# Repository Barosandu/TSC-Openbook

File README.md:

# Proiect Ariton Alexandru -- TSC -- Openbook

### Pasii de implementare
* Am creat schematicul 2D.
* Am creat PCB-ul, am intampinat niste erori:
    * **Via(hole) error** la componenta USB: am modificat footprint-ul componentei.
    * **Wire to wire error**: am rutat firele manual
* Am atribuit fiecarei componente din library cate un model 3D, si am creat placa 3d (*Push to 3D*)
* Am creat modelele pentru Display si Baterie dupa specificatiile din datasheeturi

### Diagrama block
* salvata in folder cu numele BlockSchematic.png
* Pini ESP32-C6
    * Interfetele SPI -- folosite pentru conectarea la Display
    * Este conectat la senzorul BME688 prin I2C.
    * E conectat la portul USB-C prin interfata USB
    * E conectat la butoane prin porturile GPIO

## Configurație pini ESP32-C6

| Componentă      | Pin ESP32-C6        |
|----------------|---------------------|
| Display SPI    | MOSI, CLK, CS, DC   |
| BME688         | SDA, SCL (I2C)      |
| Butoane        | GPIO1, GPIO2, GPIO3 |
| USB-C          | D+, D−, VBUS        |

### Componente Folosite

MCU: ESP32-C6-WROOM-1 (sau echivalent), datorita integrarii Wi-Fi 6, BLE 5 si a puterii de procesare ridicate.

Afisaj: Waveshare WSH-13187, e-Paper de 7.5 inch (sau echivalent), cu rezolutie 800x480.

Senzori: Bosch BME688 – pentru temperatura, umiditate, presiune si calitatea aerului.

Baterie: Baterie Li-Polimer de 2500mAh, cu circuit de protectie integrat.

Indicator nivel baterie (Fuel Gauge): Maxim MAX17048 sau echivalent.

Circuit de incarcare: Microchip MCP73831 sau echivalent.

Butoane: Comutatoare tactile Panasonic EVQ-Q2A03W (sau echivalent).

Conector USB-C: Amphenol 12401641E4R (sau echivalent).

Conector pentru card microSD: Attend Tech 112A-TAAR-R03 (sau echivalent).

Ceas in timp real (RTC): DS3231 (sau echivalent), cu supercapacitor pentru backup.

Conector Qwiic/Stemma: pentru conectarea rapida a senzorilor compatibili.

| Componenta                                      | Link                                                                 |
|------------------------------------------------|----------------------------------------------------------------------|
| adafruit_led                                   | [Link](https://www.snapeda.com/parts/KP-1608SURCK/Kingbright/view-part/?company=Politehnica+University+of+Buch&welcome=home&ref=search&t=LED+0603) |
| Button_customv1                                | [Link](https://industry.panasonic.com/global/en/products/control/switch/light-touch/number/evqpuj02k) |
| Eagle_ltspice_c                                | [Link](https://componentsearchengine.com/part-view/0402WGF3001TCE/UNI-ROYAL(Uniroyal%20Elec)) |
| ESP32_WROVER_AVX—SD0805S020S1R0                | [Link](https://ro.mouser.com/ProductDetail/KYOCERA-AVX/SD0805S020S1R0?qs=jCA%252BPfw4LHbpkAoSnwrdjw%3D%3D) |
| ESP32_WROVER_BME680_BME680                     | [Link](https://www.snapeda.com/parts/BME680/Bosch/view-part/?welcome=home) |
| ESP32_WROVER_EAGLE-LTSPICE_R                   | [Link](https://componentsearchengine.com/part-view/R0402%201%25%20100%20K%20(RC0402FR-07100KL)/YAGEO) |
| RCL_CPOL-EU                                    | [Link](https://www.snapeda.com/parts/TAJB475K025RNJ/AVX/view-part/?t=capacitor%203528&con_ref=None) |
| SJ                                             | [Link](https://grabcad.com/library/solder-jumpers-1) |
| R-URI                                          | [Link](https://componentsearchengine.com/part-view/R0402%201%25%20100%20K%20(RC0402FR-07100KL)/YAGEO) |
| ESP32_WROVER_SPARKFUN-DISCRETESEMI_MOSFET_PCH | [Link](https://componentsearchengine.com/part-view/DMG2305UX-7/Diodes%20Incorporated) |
| ESP32_WROVER_SPARKFUN-IC-POWER_MCP73831       | [Link](https://eu.mouser.com/ProductDetail/Microchip-Technology/MCP73831T-2ACI-OT?qs=yUQqVecv4qvbBQBGbHx0Mw%3D%3D) |
| TP                                             | Facut Manual |
| FH34SRJ-24S-0.5SH_99_                          | [Link](https://componentsearchengine.com/part-view/FH34SRJ-24S-0.5SH(99)/Hirose) |
| MAX17048G+T10                                  | [Link](https://www.snapeda.com/parts/MAX17048G+T10/Analog+Devices/view-part/) |
| SAMACSYS_PARTS_USB4110-GF-A                    | [Link](https://componentsearchengine.com/part-view/USB4110-GF-A/GCT%20(GLOBAL%20CONNECTOR%20TECHNOLOGY)) |
| QWIIC_CONNECTOR                                | [Link](https://www.snapeda.com/parts/PRT-14417/SparkFun%20Electronics/view-part/?t=QWIIC_CONNECTORJS-1MM) |
| 112A-TAAR-R03_ATTEND                           | [Link](https://componentsearchengine.com/part-view/112A-TAAR-R03%20ATTEND/ATTEND) |
| 744043680IND_4828-WE-TPC_WRE                   | [Link](https://componentsearchengine.com/part-view/744043680/W%C3%BCrth%20Elektronik) |
| BD5229G-TR                                     | [Link](https://componentsearchengine.com/part-view/BD5229G-TR/ROHM%20Semiconductor) |
| CPH3225A                                       | [Link](https://componentsearchengine.com/part-view/CPH3225A/Seiko%20Semiconductors) |
| DS3231SN#                                      | [Link](https://componentsearchengine.com/part-view/DS3231SN%23/Analog%20Devices) |
| ESP32-C6-WROOM-1-N8                            | [Link](https://componentsearchengine.com/part-view/ESP32-C6-WROOM-1-N8/Espressif%20Systems) |
| MBR0530                                        | [Link](https://componentsearchengine.com/part-view/MBR0530/onsemi) |
| SI1308EDL-T1-GE3                               | [Link](https://componentsearchengine.com/part-view/SI1308EDL-T1-GE3/Vishay) |
| USBLC6-2SC6Y                                   | [Link](https://componentsearchengine.com/part-view/USBLC6-2SC6Y/STMicroelectronics) |
| W25Q512JVEIQ                                   | [Link](https://componentsearchengine.com/part-view/W25Q512JVEIQ/Winbond) |
| XC6220A331MR-G                                 | [Link](https://componentsearchengine.com/part-view/XC6220A331MR-G/Torex) |

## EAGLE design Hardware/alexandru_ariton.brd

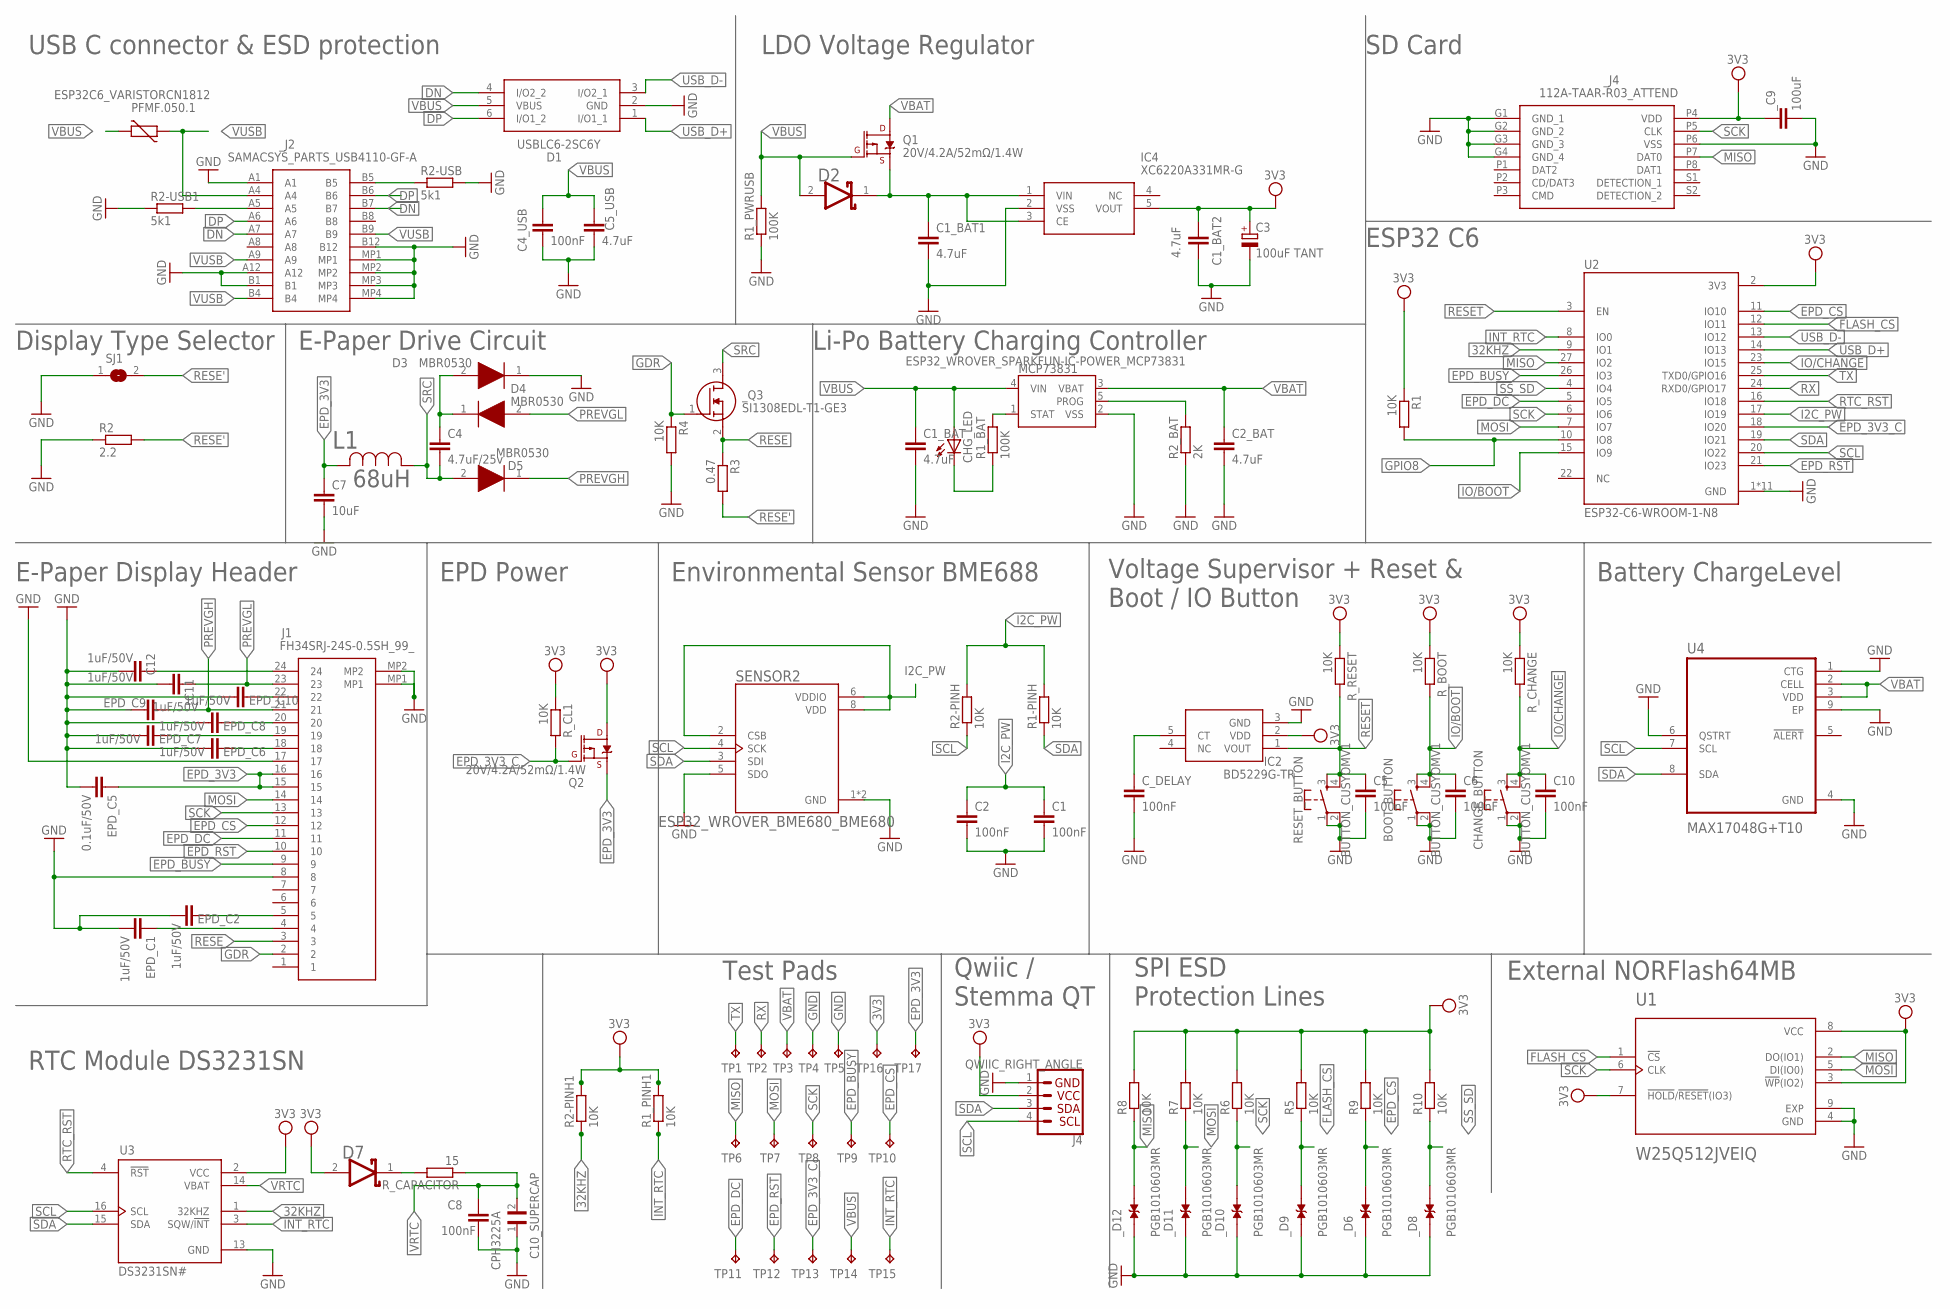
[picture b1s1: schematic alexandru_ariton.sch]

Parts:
BOOT_BUTTON: BUTTON_CUSYOMV1; MYBUTTON
C1, C2, C4_USB, C8: 100nF; EAGLE-LTSPICE_C0402
C1_BAT, C1_BAT1, C1_BAT2, C2_BAT, C5_USB: 4.7uF; EAGLE-LTSPICE_C0402
C3: 100uF TANT; RCL_CT3528
C4: 4.7uF/25v; EAGLE-LTSPICE_C0402
C5, C6, C10: 100nF; ESP32_WROVER_EAGLE-LTSPICE_C0402
C7: 10uF; EAGLE-LTSPICE_C0402
C10_SUPERCAP: CPH3225A; CAPCP3225X100N
C11, C12: 1uF/50V; EAGLE-LTSPICE_C0402
CHANGE_BUTTON: BUTTON_CUSYOMV1; MYBUTTON
CHG_LED: ADAFRUIT_LEDCHIP-LED0603; ADAFRUIT_CHIP-LED0603
C_DELAY: 100nF; ESP32_WROVER_EAGLE-LTSPICE_C0402
D1: USBLC6-2SC6Y; SOT95P280X145-6N
D2, D7: ESP32_WROVER_AVX---SD0805S020S1R0_AVX_SD0805S020S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; ESP32_WROVER_AVX---SD0805S020S1R0_AVX_SD0805S020S1R0_0
D3, D4, D5: MBR0530; SOD3716X135N
EPD_C1, EPD_C2, EPD_C6, EPD_C7, EPD_C8, EPD_C9, EPD_C10: 1uF/50V; EAGLE-LTSPICE_C0402
EPD_C5: 0.1uF/50V; EAGLE-LTSPICE_C0402
IC2: BD5229G-TR; SOT95P280X125-5N
IC4: XC6220A331MR-G; SOT95P280X120-5N
J1: FH34SRJ-24S-0.5SH_99_; FH34SRJ24S05SH99
J4: QWIIC_RIGHT_ANGLE; JST04_1MM_RA
L1: 68uH; IND_4828-WE-TPC_WRE
MCP73831: ESP32_WROVER_SPARKFUN-IC-POWER_MCP73831; ESP32_WROVER_SPARKFUN-IC-POWER_SOT23-5
PFMF.050.1: ESP32C6_VARISTORCN1812; ESP32C6_VARISTOR_CT/CN1812
Q1, Q2: 20V/4.2A/52mΩ/1.4W; ESP32_WROVER_SPARKFUN-DISCRETESEMI_SOT23-3
R1, R1-PINH, R1_PINH1, R2-PINH, R2-PINH1, R4, R5, R6, R7, R8, R9, R10: 10K; ESP32_WROVER_EAGLE-LTSPICE_R0402
R1_BAT, R1_PWRUSB: 100K; ESP32_WROVER_EAGLE-LTSPICE_R0402
R2: 2.2; ESP32_WROVER_EAGLE-LTSPICE_R0402
R2-USB, R2-USB1: 5k1; ESP32_WROVER_EAGLE-LTSPICE_R0402
R2_BAT: 2K; ESP32_WROVER_EAGLE-LTSPICE_R0402
R3: 0.47; ESP32_WROVER_EAGLE-LTSPICE_R0402
RESET_BUTTON: BUTTON_CUSYOMV1; MYBUTTON
R_BOOT: 10K; ESP32_WROVER_EAGLE-LTSPICE_R0402
R_CAPACITOR: 15; ESP32_WROVER_EAGLE-LTSPICE_R0402
R_CHANGE: 10K; ESP32_WROVER_EAGLE-LTSPICE_R0402
R_CL1: 10K; ESP32_WROVER_EAGLE-LTSPICE_R0402
R_RESET: 10K; ESP32_WROVER_EAGLE-LTSPICE_R0402
SENSOR2: ESP32_WROVER_BME680_BME680; ESP32_WROVER_BME680_PSON80P300X300X100-8N
SJ1: SJ
TP1, TP2, TP3, TP4, TP5, TP6, TP7, TP8, TP9, TP10, TP11, TP12, TP13, TP14, TP15, TP16, TP17: TPTP20R; TP20R
U1: W25Q512JVEIQ; SON127P600X800X80-9N
U2: ESP32-C6-WROOM-1-N8; XCVR_ESP32-C6-WROOM-1-N8
U3: DS3231SN#; SOIC127P1032X265-16N
U4: MAX17048G+T10; SON50P200X200X80-9N
_C9: 100uF; EAGLE-LTSPICE_C0402
_D6, _D8, _D9, _D10, _D11, _D12: PGB1010603MR; DIOC1608X36N
_J2: SAMACSYS_PARTS_USB4110-GF-A; SAMACSYS_PARTS_USB4110GFA
_J4: 112A-TAAR-R03_ATTEND; 112ATAARR03ATTEND
_Q3: SI1308EDL-T1-GE3; SOT65P210X110-3N

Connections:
3V3: C1_BAT2.1, C3.+, D7.2 (ANODE), IC2.2 (VDD), IC4.5 (VOUT), J4.2, Q2.3 (D), R1.1, R1_PINH1.2, R2-PINH1.2, R5.2, R6.2, R7.2, R8.2, R9.2, R10.2, R_BOOT.1, R_CHANGE.1, R_CL1.1, R_RESET.1, TP16.TP, U1.3 (!WP!(IO2)), U1.7 (!HOLD!/!RESET!(IO3)), U1.8 (VCC), U2.2 (3V3), U3.2 (VCC), _C9.1, _J4.P4 (VDD)
32KHZ: R2-PINH1.1, U2.9 (IO1), U3.1 (32KHZ)
DN: D1.4 (I/O2_2), _J2.A7, _J2.B7
DP: D1.6 (I/O1_2), _J2.A6, _J2.B6
EPD_3V3: C7.1, EPD_C5.1, J1.15, J1.16, L1.2, Q2.2 (S), TP17.TP
EPD_3V3_C: Q2.1 (G), R_CL1.2, TP13.TP, U2.18 (IO20)
EPD_BUSY: J1.9, TP9.TP, U2.26 (IO3)
EPD_CS: J1.12, R9.1, TP10.TP, U2.11 (IO10), _D6.2
EPD_DC: J1.11, TP11.TP, U2.5 (IO5)
EPD_RST: J1.10, TP12.TP, U2.21 (IO23)
FLASH_CS: R5.1, U1.1 (!CS), U2.12 (IO11), _D9.2
GDR: J1.2, R4.1, _Q3.1 (G)
GND: BOOT_BUTTON.1, BOOT_BUTTON.2, C1.2, C1_BAT.2, C1_BAT1.2, C1_BAT2.2, C2.2, C2_BAT.2, C3.-, C4_USB.2, C5.2, C5_USB.2, C6.2, C7.2, C8.2, C10.2, C10_SUPERCAP.1, C11.2, C12.2, CHANGE_BUTTON.1, CHANGE_BUTTON.2, C_DELAY.2, D1.2 (GND), D3.1 (K), EPD_C1.2, EPD_C2.2, EPD_C5.2, EPD_C6.2, EPD_C7.2, EPD_C8.2, EPD_C9.2, EPD_C10.2, IC2.3 (GND), IC4.2 (VSS), J1.8, J1.17, J1.MP1, J1.MP2, J4.1, MCP73831.2 (VSS), R1_PWRUSB.1, R2.1, R2-USB.2, R2-USB1.1, R2_BAT.1, R4.2, RESET_BUTTON.1, RESET_BUTTON.2, SENSOR2.1 (GND), SENSOR2.5 (SDO), SENSOR2.7 (GND), SJ1.1, TP4.TP, TP5.TP, U1.4 (GND), U1.9 (EXP), U2.1 (GND), U2.28 (GND), U2.29_1 (GND), U2.29_2 (GND), U2.29_3 (GND), U2.29_4 (GND), U2.29_5 (GND), U2.29_6 (GND), U2.29_7 (GND), U2.29_8 (GND), U2.29_9 (GND), U3.13 (GND), U4.1 (CTG), U4.4 (GND), U4.6 (QSTRT), U4.9 (EP), _C9.2, _D6.1, _D8.1, _D9.1, _D10.1, _D11.1, _D12.1, _J2.A1, _J2.A12, _J2.B1, _J2.B12, _J2.MP1, _J2.MP2, _J2.MP3, _J2.MP4, _J4.G1 (GND_1), _J4.G2 (GND_2), _J4.G3 (GND_3), _J4.G4 (GND_4), _J4.P6 (VSS)
GPIO8: R1.2, U2.10 (IO8)
I2C_PW: C1.1, C2.1, R1-PINH.2, R2-PINH.2, SENSOR2.2 (CSB), SENSOR2.6 (VDDIO), SENSOR2.8 (VDD), U2.17 (IO19)
INT_RTC: R1_PINH1.1, TP15.TP, U2.8 (IO0), U3.3 (SQW/!INT)
IO/BOOT: BOOT_BUTTON.3, BOOT_BUTTON.4, C6.1, R_BOOT.2, U2.15 (IO9)
IO/CHANGE: C10.1, CHANGE_BUTTON.3, CHANGE_BUTTON.4, R_CHANGE.2, U2.23 (IO15)
MISO: R8.1, TP6.TP, U1.2 (DO(IO1)), U2.27 (IO2), _D12.2, _J4.P7 (DAT0)
MOSI: J1.14, R7.1, TP7.TP, U1.5 (DI(IO0)), U2.7 (IO7), _D11.2
unnamed: R2-USB.1, _J2.B5
unnamed: R2-USB1.2, _J2.A5
unnamed: C1_BAT1.1, D2.1 (CATHODE), IC4.1 (VIN), IC4.3 (CE), Q1.2 (S)
unnamed: MCP73831.1 (STAT), R1_BAT.2
unnamed: C4.1, D3.2 (A), D4.1 (K)
unnamed: CHG_LED.C, R1_BAT.1
unnamed: MCP73831.5 (PROG), R2_BAT.2
unnamed: C12.1, J1.24
unnamed: EPD_C10.1, J1.22
unnamed: EPD_C8.1, J1.20
unnamed: EPD_C7.1, J1.19
unnamed: EPD_C6.1, J1.18
unnamed: D7.1 (CATHODE), R_CAPACITOR.2
unnamed: C_DELAY.1, IC2.5 (CT)
unnamed: EPD_C1.1, J1.4
unnamed: EPD_C2.1, J1.5
PREVGH: D5.1 (K), EPD_C9.1, J1.21
PREVGL: C11.1, D4.2 (A), J1.23
RESE: J1.3, R3.1, _Q3.2 (S)
RESE': R2.2, R3.2, SJ1.2
RESET: C5.1, IC2.1 (VOUT), RESET_BUTTON.3, RESET_BUTTON.4, R_RESET.2, U2.3 (EN)
RTC_RST: U2.16 (IO18), U3.4 (!RST)
RX: TP2.TP, U2.24 (RXD0/GPIO17)
SCK: J1.13, R6.1, TP8.TP, U1.6 (CLK), U2.6 (IO6), _D10.2, _J4.P5 (CLK)
SCL: J4.4, R2-PINH.1, SENSOR2.4 (SCK), U2.20 (IO22), U3.16 (SCL), U4.7 (SCL)
SDA: J4.3, R1-PINH.1, SENSOR2.3 (SDI), U2.19 (IO21), U3.15 (SDA), U4.8 (SDA)
SRC: C4.2, D5.2 (A), L1.1, _Q3.3 (D)
SS_SD: R10.1, U2.4 (IO4), _D8.2
TX: TP1.TP, U2.25 (TXD0/GPIO16)
USB_D+: D1.1 (I/O1_1), U2.14 (IO13)
USB_D-: D1.3 (I/O2_1), U2.13 (IO12)
VBAT: C2_BAT.1, MCP73831.3 (VBAT), Q1.3 (D), TP3.TP, U4.2 (CELL), U4.3 (VDD)
VBUS: C1_BAT.1, C4_USB.1, C5_USB.1, CHG_LED.A, D1.5 (VBUS), D2.2 (ANODE), MCP73831.4 (VIN), PFMF.050.1.2, Q1.1 (G), R1_PWRUSB.2, TP14.TP
VRTC: C8.1, C10_SUPERCAP.2, R_CAPACITOR.1, U3.14 (VBAT)
VUSB: PFMF.050.1.1, _J2.A4, _J2.A9, _J2.B4, _J2.B9

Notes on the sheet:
USB C connector & ESD protection
LDO Voltage Regulator
SD Card
Display Type Selector
E-Paper Drive Circuit
Li-Po Battery Charging Controller
ESP32 C6
E-Paper Display Header
EPD Power
Environmental Sensor BME688
Voltage Supervisor + Reset & Boot / IO Button
Battery ChargeLevel
RTC Module DS3231SN
Test Pads
Qwiic / Stemma QT
SPI ESD Protection Lines
External NORFlash64MB

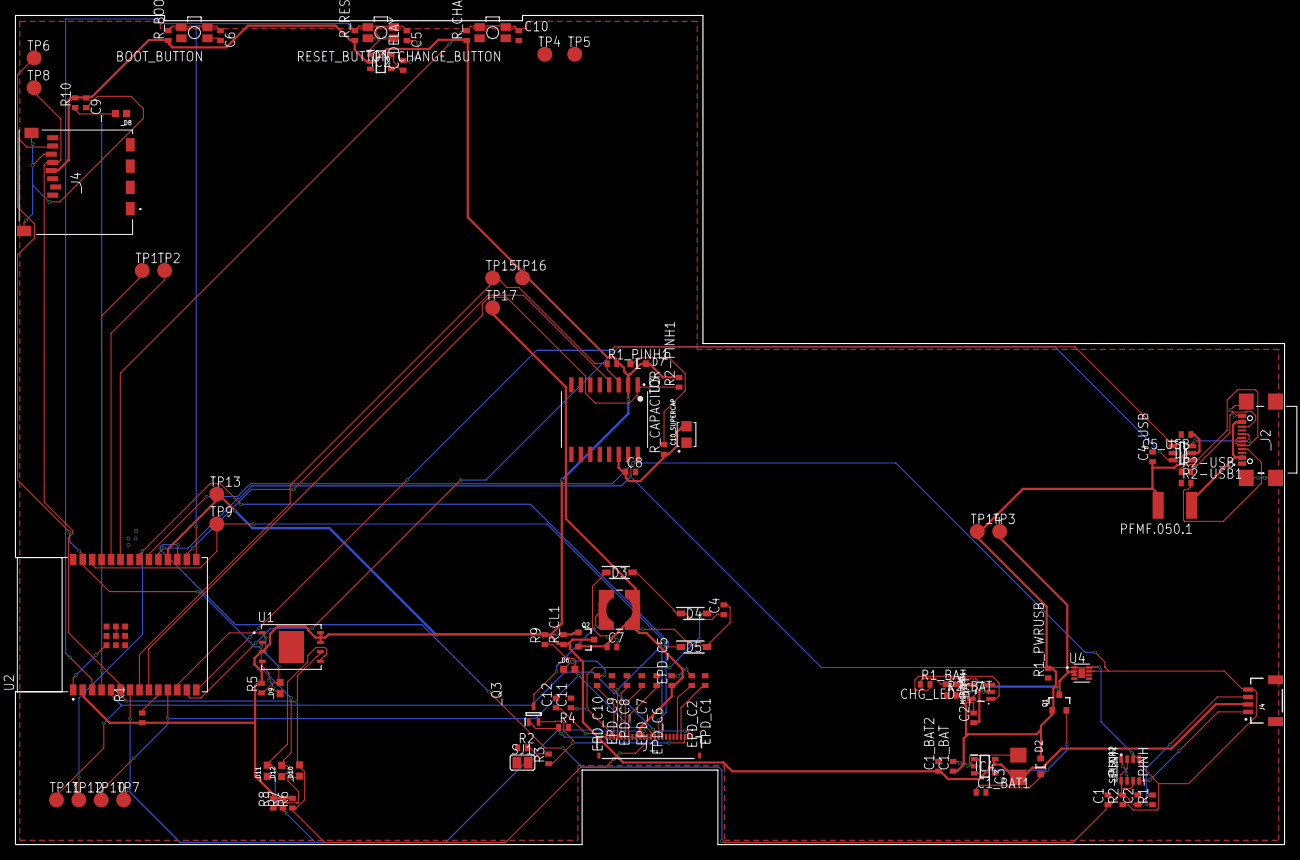
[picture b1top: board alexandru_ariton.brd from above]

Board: 2 copper layers, 170.2 x 111.2 mm, 103 parts (0 on the bottom side), 55 nets.

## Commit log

2025-04-05 Totul inafara de readme
2025-04-05 Added license
2025-04-05 READMEEE
2025-04-05 READMEEE more 2
2025-04-05 readme si mai final
2025-04-14 Fixed: via stitching, big labels, no holes in base screen
2025-04-14 Renamed a file

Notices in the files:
parts and their libraries:
COPYRIGHT: Copyright (C) 2024 Ultra Librarian. All rights reserved.
